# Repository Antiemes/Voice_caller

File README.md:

# Voice_caller
Voice caller aka. pofazogep

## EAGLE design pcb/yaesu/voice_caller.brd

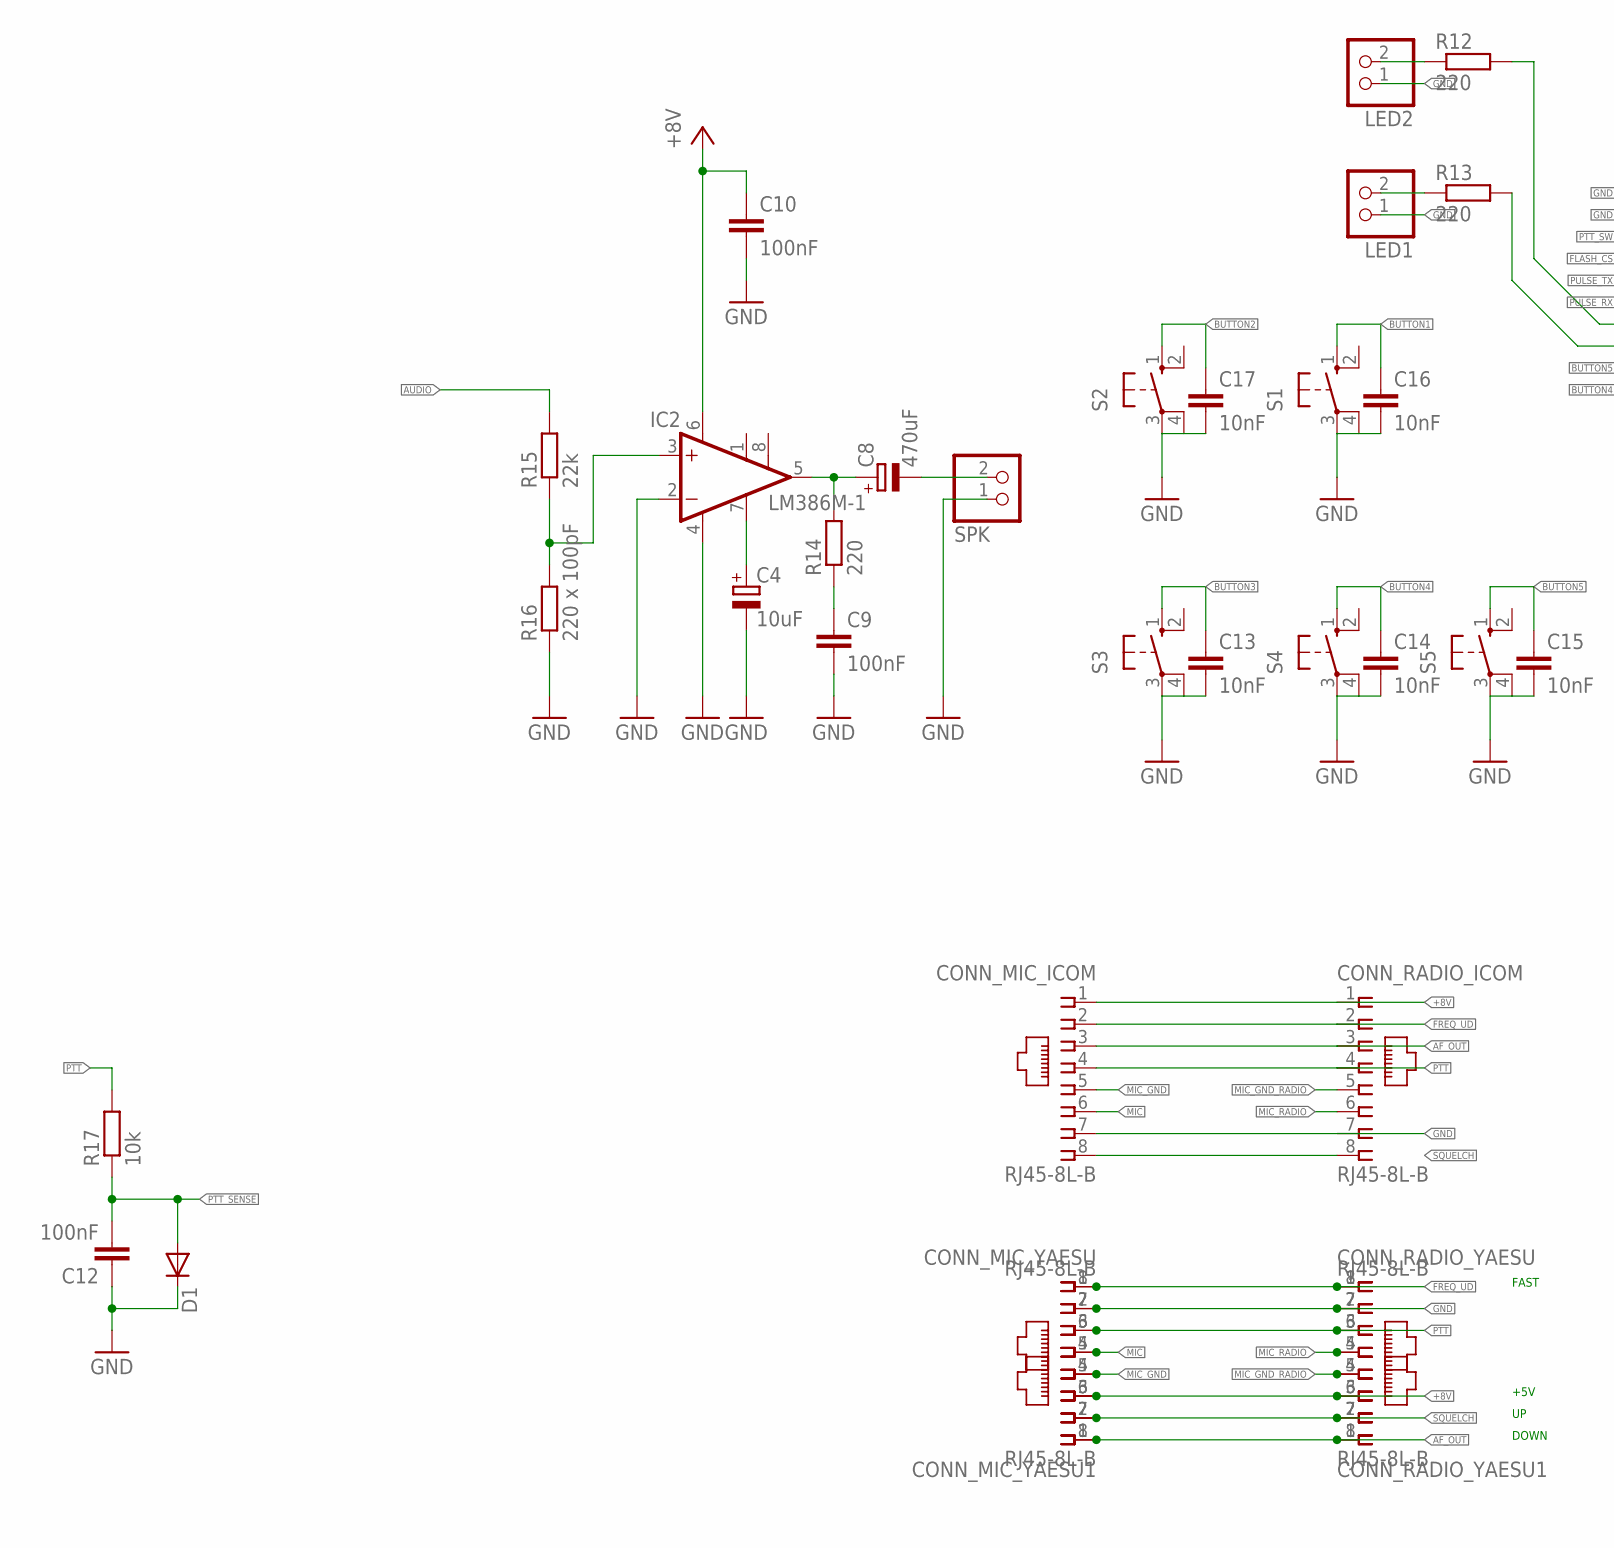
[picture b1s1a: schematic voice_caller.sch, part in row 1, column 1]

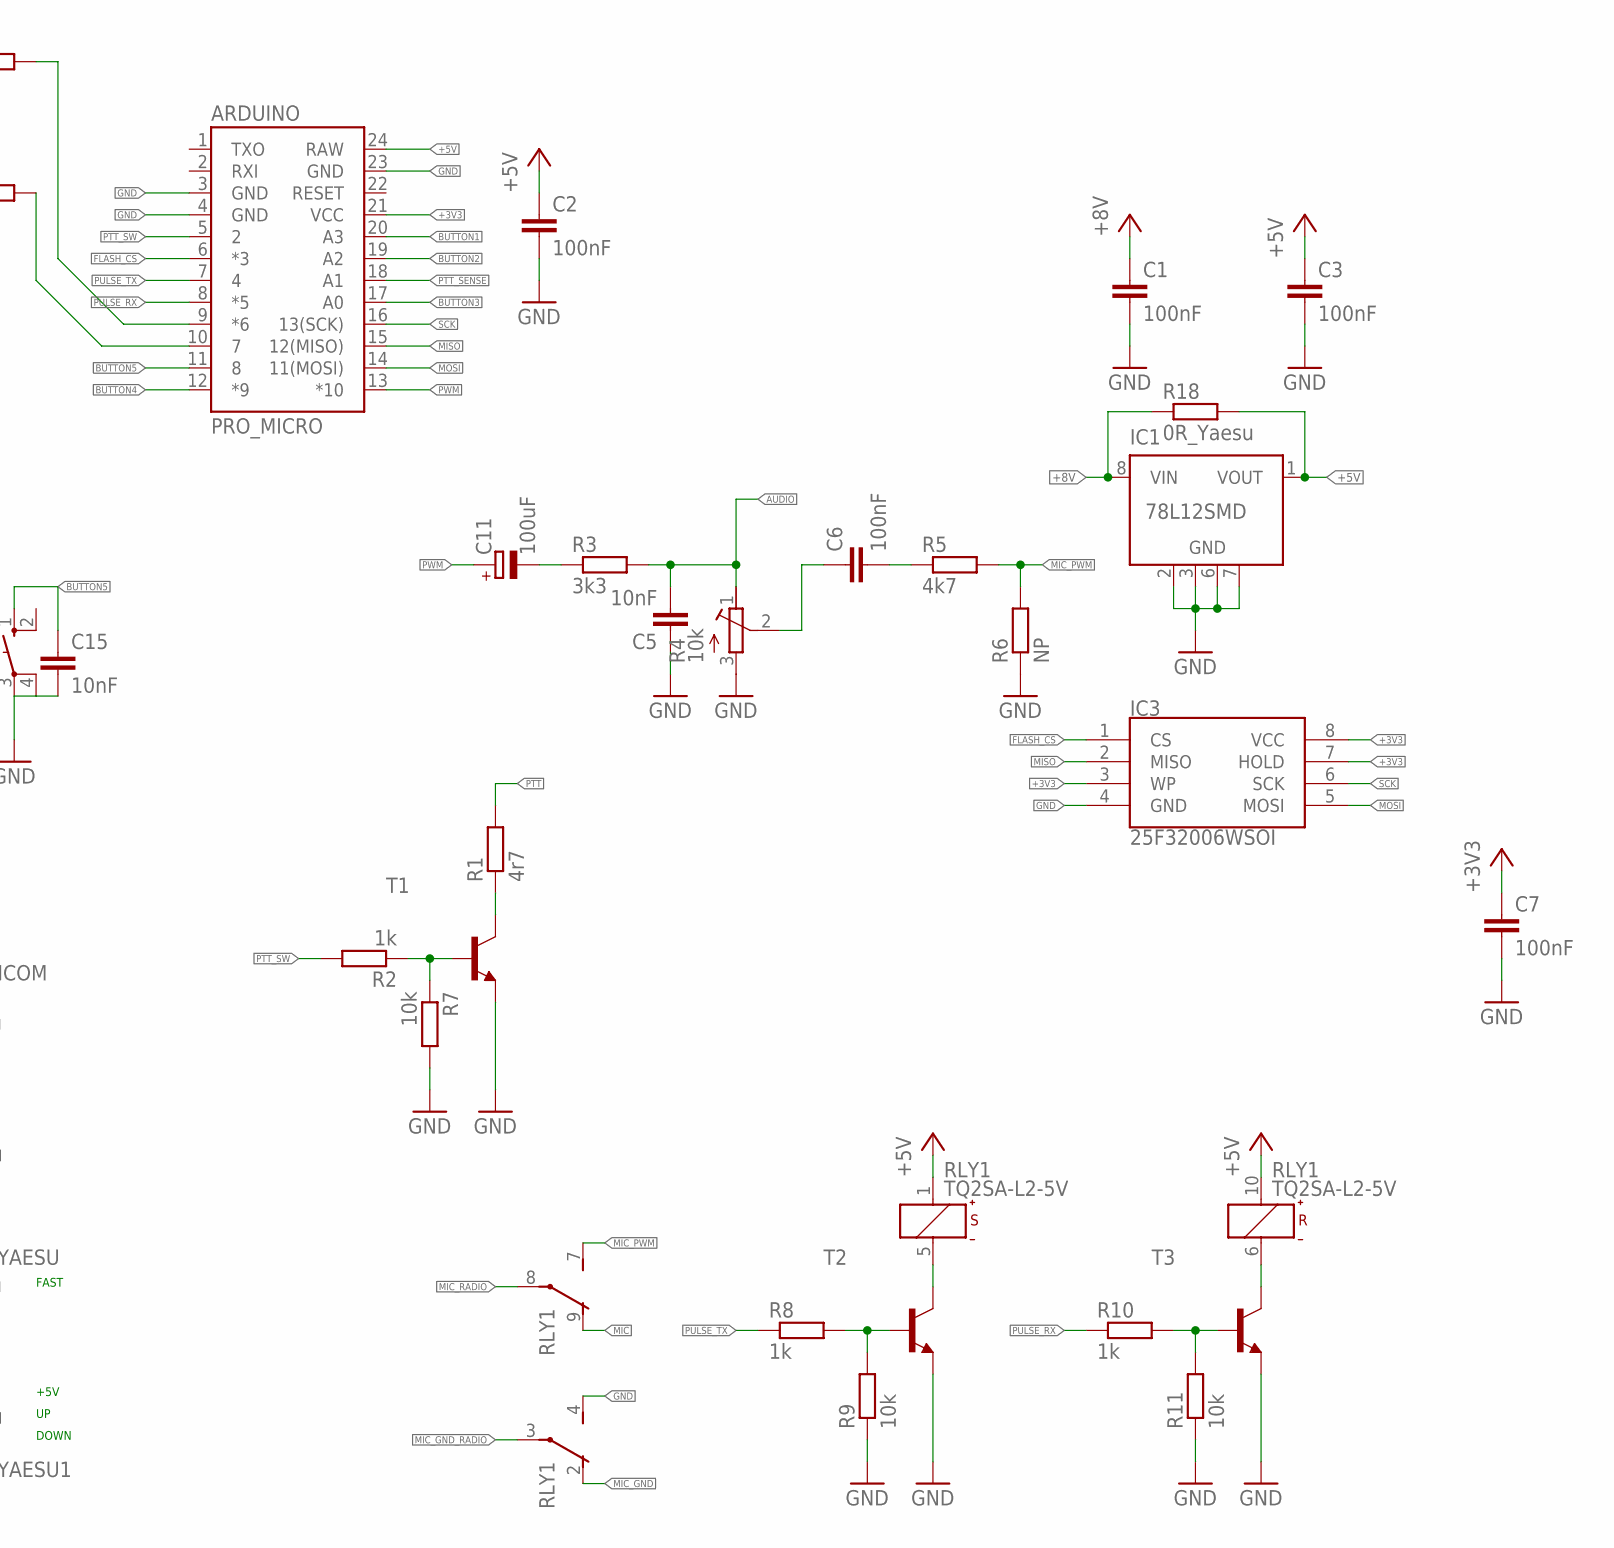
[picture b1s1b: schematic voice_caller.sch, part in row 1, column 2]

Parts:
ARDUINO: PRO_MICRO; SPARKFUN_PRO_MICRO
C1, C2, C3, C6, C7, C9, C10, C12: 100nF; C1206K
C4: 10uF; E2,5-6
C5, C13, C14, C15, C16, C17: 10nF; C1206K
C8: 470uF; E2,5-6
C11: 100uF; E2,5-6
CONN_MIC_ICOM: RJ45-8L-B; RJ45-NO-SHIELD
CONN_MIC_YAESU, CONN_MIC_YAESU1: RJ45-8L-B; RJ45-NO-SHIELD
CONN_RADIO_ICOM: RJ45-8L-B; RJ45-NO-SHIELD
CONN_RADIO_YAESU, CONN_RADIO_YAESU1: RJ45-8L-B; RJ45-NO-SHIELD
D1: DIODE-SOD80C; SOD80C
IC1: 78L12SMD; SO08
IC2: LM386M-1; SO08
IC3: 25F32006WSOI; SO08-EIAJ
LED1, LED2: PINHD-1X2; 1X02
R1: 4r7; M1206
R2, R8, R10: 1k; M1206
R3: 3k3; M1206
R4: 10k; RTRIMT93XB
R5: 4k7; M1206
R6: NP; M1206
R7, R9, R11, R17: 10k; M1206
R12, R13, R14: 220; M1206
R15: 22k; M1206
R16: 220 x 100pF; M1206
R18: 0R_Yaesu; M1206
RLY1: TQ2SA-L2-5V; TQ-SA
S1, S2, S3, S4, S5: 10-XX; B3F-10XX
SPK: PINHD-1X2; 1X02
T1, T2, T3: MMBT3904LT1-NPN-SOT23-BEC; SOT23-BEC

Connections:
+3V3: ARDUINO.21 (VCC), C7.1, IC3.3 (WP), IC3.7 (HOLD), IC3.8 (VCC)
+5V: ARDUINO.24 (RAW), C2.1, C3.1, IC1.1 (VOUT), R18.2, RLY1.1 (+), RLY1.10 (+)
+8V: C1.1, C10.1, CONN_MIC_ICOM.1, CONN_MIC_YAESU.6, CONN_MIC_YAESU1.3, CONN_RADIO_ICOM.1, CONN_RADIO_YAESU.6, CONN_RADIO_YAESU1.3, IC1.8 (VIN), IC2.6 (VS), R18.1
AF_OUT: CONN_MIC_ICOM.3, CONN_MIC_YAESU.8, CONN_MIC_YAESU1.1, CONN_RADIO_ICOM.3, CONN_RADIO_YAESU.8, CONN_RADIO_YAESU1.1
AUDIO: C5.2, R3.2, R4.1 (E), R15.2
BUTTON1: ARDUINO.20 (A3), C16.1, S1.1 (S)
BUTTON2: ARDUINO.19 (A2), C17.1, S2.1 (S)
BUTTON3: ARDUINO.17 (A0), C13.1, S3.1 (S)
BUTTON4: ARDUINO.12 (*9), C14.1, S4.1 (S)
BUTTON5: ARDUINO.11 (8), C15.1, S5.1 (S)
FLASH_CS: ARDUINO.6 (*3), IC3.1 (CS)
FREQ_UD: CONN_MIC_ICOM.2, CONN_MIC_YAESU.1, CONN_MIC_YAESU1.8, CONN_RADIO_ICOM.2, CONN_RADIO_YAESU.1, CONN_RADIO_YAESU1.8
GND: ARDUINO.3 (GND), ARDUINO.4 (GND), ARDUINO.23 (GND), C1.2, C2.2, C3.2, C4.-, C5.1, C7.2, C9.2, C10.2, C12.1, C13.2, C14.2, C15.2, C16.2, C17.2, CONN_MIC_ICOM.7, CONN_MIC_YAESU.2, CONN_MIC_YAESU1.7, CONN_RADIO_ICOM.7, CONN_RADIO_YAESU.2, CONN_RADIO_YAESU1.7, D1.C, IC1.2 (GND), IC1.3 (GND), IC1.6 (GND), IC1.7 (GND), IC2.2 (-IN), IC2.4 (GND), IC3.4 (GND), LED1.1, LED2.1, R4.3 (A), R6.1, R7.2, R9.1, R11.1, R16.1, RLY1.4 (S), S1.3, S1.4 (P1), S2.3, S2.4 (P1), S3.3, S3.4 (P1), S4.3, S4.4 (P1), S5.3, S5.4 (P1), SPK.1, T1.E, T2.E, T3.E
MIC: CONN_MIC_ICOM.6, CONN_MIC_YAESU.4, CONN_MIC_YAESU1.5, RLY1.9 (O)
MIC_GND: CONN_MIC_ICOM.5, CONN_MIC_YAESU.5, CONN_MIC_YAESU1.4, RLY1.2 (O)
MIC_GND_RADIO: CONN_RADIO_ICOM.5, CONN_RADIO_YAESU.5, CONN_RADIO_YAESU1.4, RLY1.3
MIC_PWM: R5.2, R6.2, RLY1.7 (S)
MIC_RADIO: CONN_RADIO_ICOM.6, CONN_RADIO_YAESU.4, CONN_RADIO_YAESU1.5, RLY1.8
MISO: ARDUINO.15 (12(MISO)), IC3.2 (MISO)
MOSI: ARDUINO.14 (11(MOSI)), IC3.5 (MOSI)
unnamed: C11.-, R3.1
unnamed: IC2.3 (+IN), R15.1, R16.2
unnamed: C6.2, R5.1
unnamed: LED2.2, R12.1
unnamed: R2.1, R7.1, T1.B
unnamed: C6.1, R4.2 (S)
unnamed: C4.+, IC2.7 (BYPASS)
unnamed: R1.1, T1.C
unnamed: LED1.2, R13.1
unnamed: RLY1.5 (-), T2.C
unnamed: R8.2, R9.2, T2.B
unnamed: ARDUINO.9 (*6), R12.2
unnamed: RLY1.6 (-), T3.C
unnamed: R10.2, R11.2, T3.B
unnamed: ARDUINO.10 (7), R13.2
unnamed: C8.+, IC2.5 (OUT), R14.2
unnamed: C9.1, R14.1
unnamed: C8.-, SPK.2
PTT: CONN_MIC_ICOM.4, CONN_MIC_YAESU.3, CONN_MIC_YAESU1.6, CONN_RADIO_ICOM.4, CONN_RADIO_YAESU.3, CONN_RADIO_YAESU1.6, R1.2, R17.2
PTT_SENSE: ARDUINO.18 (A1), C12.2, D1.A, R17.1
PTT_SW: ARDUINO.5 (2), R2.2
PULSE_RX: ARDUINO.8 (*5), R10.1
PULSE_TX: ARDUINO.7 (4), R8.1
PWM: ARDUINO.13 (*10), C11.+
SCK: ARDUINO.16 (13(SCK)), IC3.6 (SCK)
SQUELCH: CONN_MIC_ICOM.8, CONN_MIC_YAESU.7, CONN_MIC_YAESU1.2, CONN_RADIO_ICOM.8, CONN_RADIO_YAESU.7, CONN_RADIO_YAESU1.2

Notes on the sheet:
FAST
+5V
DOWN

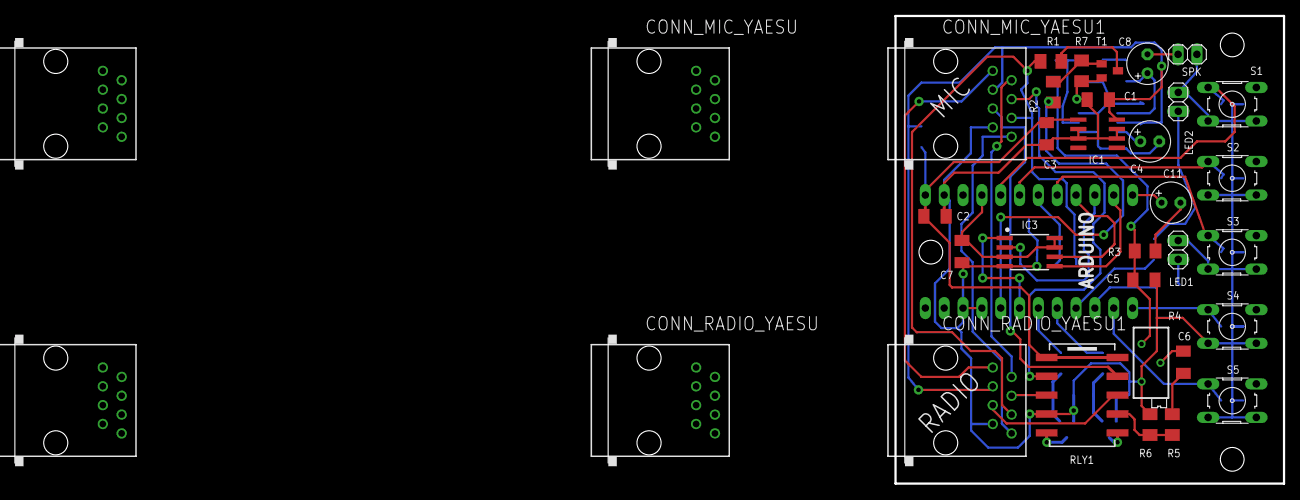
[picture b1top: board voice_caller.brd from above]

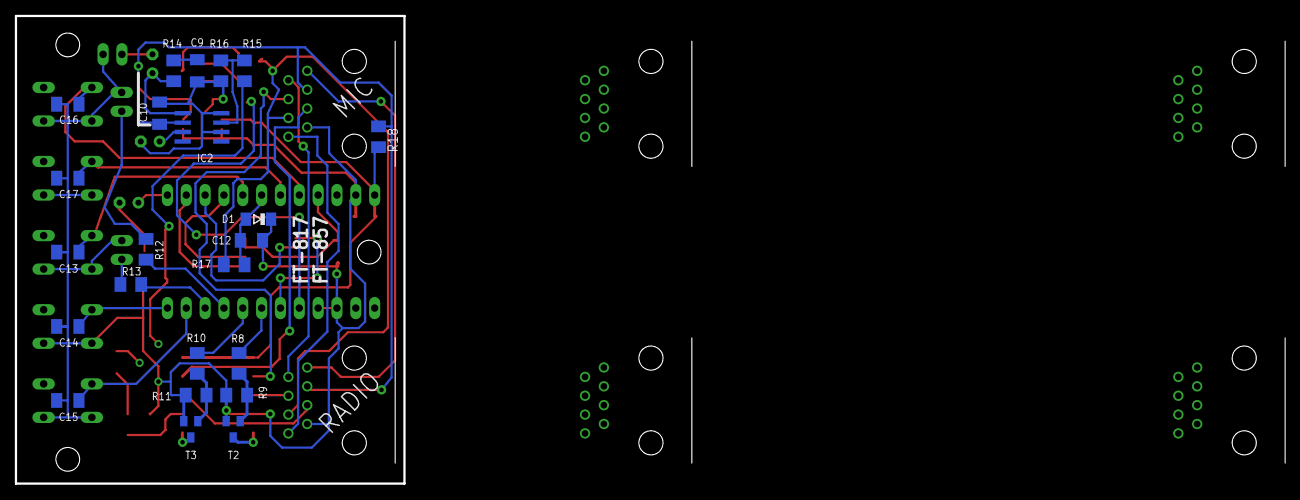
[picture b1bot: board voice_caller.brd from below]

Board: 2 copper layers, 52.4 x 63.1 mm, 58 parts (23 on the bottom side), 46 nets.

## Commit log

2019-01-29 Arduino nano lib added
2019-01-29 Firmware added
2019-01-29 Image maker script added
2019-01-31 PCB first sketch added
2019-02-04 Who knows
2019-02-09 Pro micro board added
2019-02-09 Nano changed to pro micro
2019-02-11 RJ-45 connected
2019-05-05 Some progress with the PCB
2019-05-05 ProMicro pads modified
2019-05-05 More progress with the PCB
2019-05-06 All but switches
2019-05-09 Buttons and bistable relay added, PTT thing is missing.
2019-05-10 PTT circuit added
2019-05-10 Analog pins modified
2019-07-12 Routing done
2019-07-12 Headers for LEDs added
2019-07-12 Mounting holes
2019-08-04 Missing nets for flash routed.
2019-08-04 RC values added.
2019-08-06 SPI pins changed according to Pro Micro.
2019-08-06 Wiring in repeating the audio playback.
2019-08-06 Commenting out GPIO related stuff.
2019-08-06 Firmware moved to platformio
2019-08-06 At least I have a beep now.
2019-08-07 PWM settings for new pin.
2019-08-07 Firmware directory moved.
2019-08-07 LED settings added.
2019-08-07 Relay GPIO initialization
2019-08-07 PTT switch code.
2019-08-07 Removed mispelled directory
2019-08-07 Arduino platfrom removed.
2019-08-07 Code ported to ATmega32u4.
2019-08-09 Relay functions added.
2019-08-09 Relay control added.
2019-08-09 Values adjusted.
2019-08-11 Timer frequency is now correct.
2019-08-13 Flash IC replaced and almost routed.
2019-08-15 Flash routed, PTT sense changed.
2019-08-15 Monitor amp added and routed.
2019-08-15 Bypass capacitor added for LM386.
2019-08-19 Flash IC from Sparkfun lib.
2019-08-20 Script makes text file for flash upload.
2019-08-20 PlatformIO stuff removed
2019-08-20 Firmware code without PlatformIO, USB CDC and flash write support added.
2019-08-20 Object files removed. Oops.
2019-08-21 PTT sensing added.
2019-08-22 PTT sensing circuity added.
2019-08-22 Filter capacitors added to pushbuttons
2019-08-22 PTT sensing modified.
2019-08-22 RJ-45 connectors moves 1.3mm inwards.
2019-08-23 Timing of PTT sensing modified.
2019-08-23 Configurable timing.
2019-09-03 Final adjustments.
2019-10-24 AF amp attenuator changed.
2019-10-24 Jumper wire added.
2019-11-05 Flash unlock command added.
2019-11-05 A big issue with timing was fixed.
2019-11-05 Blocksize modified.
2019-11-05 Attenuator changed, Yaesu connector added.
2019-11-20 Microchip Flash type added.
2019-11-28 Pot. value added.
2020-05-28 SampleCounter clash removed
2020-05-28 Some warnings eliminated.
2020-07-08 Icom version moved to another folder.
2020-07-08 Yaesu version.
2020-07-21 Connector connections corredted.
2021-05-10 3D printed enclosure added
2021-07-07 Style changed
2021-07-07 Magnets added
2023-08-14 Bigger speaker

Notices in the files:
parts and their libraries:
SparkFun-Boards: Licensing: Creative Commons ShareAlike 4.0 International - https://creativecommons.org/licenses/by-sa/4.0
